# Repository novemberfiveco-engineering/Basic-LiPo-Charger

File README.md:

# Basic LiPo Charger

[This breakout](https://www.tindie.com/products/novemberfive/basic-lipo-battery-charger/) uses the [MCP73831](http://www.microchip.com/wwwproducts/en/en024903). It's ideal for charging LiPo batteries in space-limited, cost-sensitive applications and designed with adjustable charging rate (15mA - 500mA).

## Features

* Programmable Charge Current: 15mA to 500mA
* Provided with status LED
* Battery connection JST-type
* Micro-USB power connector
* Input voltage 3.75 - 6V
* Provided place to fork current
* Demensions: 31.0 x 12.8 mm

For more information about the MCP73831 please click [here](http://www.microchip.com/wwwproducts/en/en024903)

## Where to get?
You can buy this item on Tindie from the [November Five's hardware shop](https://www.tindie.com/products/novemberfive/basic-lipo-battery-charger/).

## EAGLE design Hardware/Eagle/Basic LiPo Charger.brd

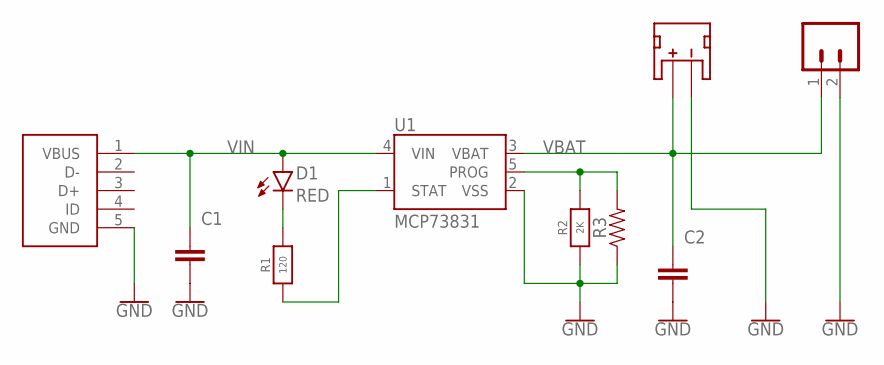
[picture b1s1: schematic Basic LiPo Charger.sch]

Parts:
C1, C2: 4.7uF; C0603
D1: RED; LED-0603
J1: USB-CON-5PIN-105017-0001; USB-MICRO-MOLEX-105017-0001
J2: JST_2MM_MALE; JST-2-SMD
J3: CONN_02; 1X02
R1: 120; R0603
R2: 2K; R0603
R3: 10MOHM-HORIZ-1/4W-5%; AXIAL-0.3
U1: MCP73831; SOT23-5

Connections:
GND: C1.2, C2.2, J1.5 (GND), J2.1 (-), J3.2, R2.1, R3.P$1 (1), U1.2 (VSS)
unnamed: D1.C, R1.2
PROG: R2.2, R3.P$2 (2), U1.5 (PROG)
STAT: R1.1, U1.1 (STAT)
VBAT: C2.1, J2.2 (+), J3.1, U1.3 (VBAT)
VIN: C1.1, D1.A, J1.1 (VBUS), U1.4 (VIN)

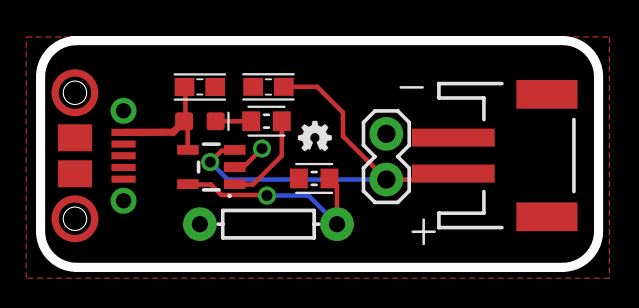
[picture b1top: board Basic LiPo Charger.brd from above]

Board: 2 copper layers, 31.0 x 12.6 mm, 12 parts (0 on the bottom side), 6 nets.

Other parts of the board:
U$1: LOGO-NOVEMERFIVE-5SCALE
U$2: LOGO-OSHWA

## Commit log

2017-05-10 Added readme
2017-05-10 Updated link
2017-05-16 Changed resistor value
2017-05-16 Move via
2017-05-16 Add BOM

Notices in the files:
parts and their libraries:
SparkFun-LED: Licensing: Creative Commons ShareAlike 4.0 International - https://creativecommons.org/licenses/by-sa/4.0
